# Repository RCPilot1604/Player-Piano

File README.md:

**Work in progress**
Detailed writeup here: https://urbanmakerkraft.com/2024/08/10/player-piano-project-v1/

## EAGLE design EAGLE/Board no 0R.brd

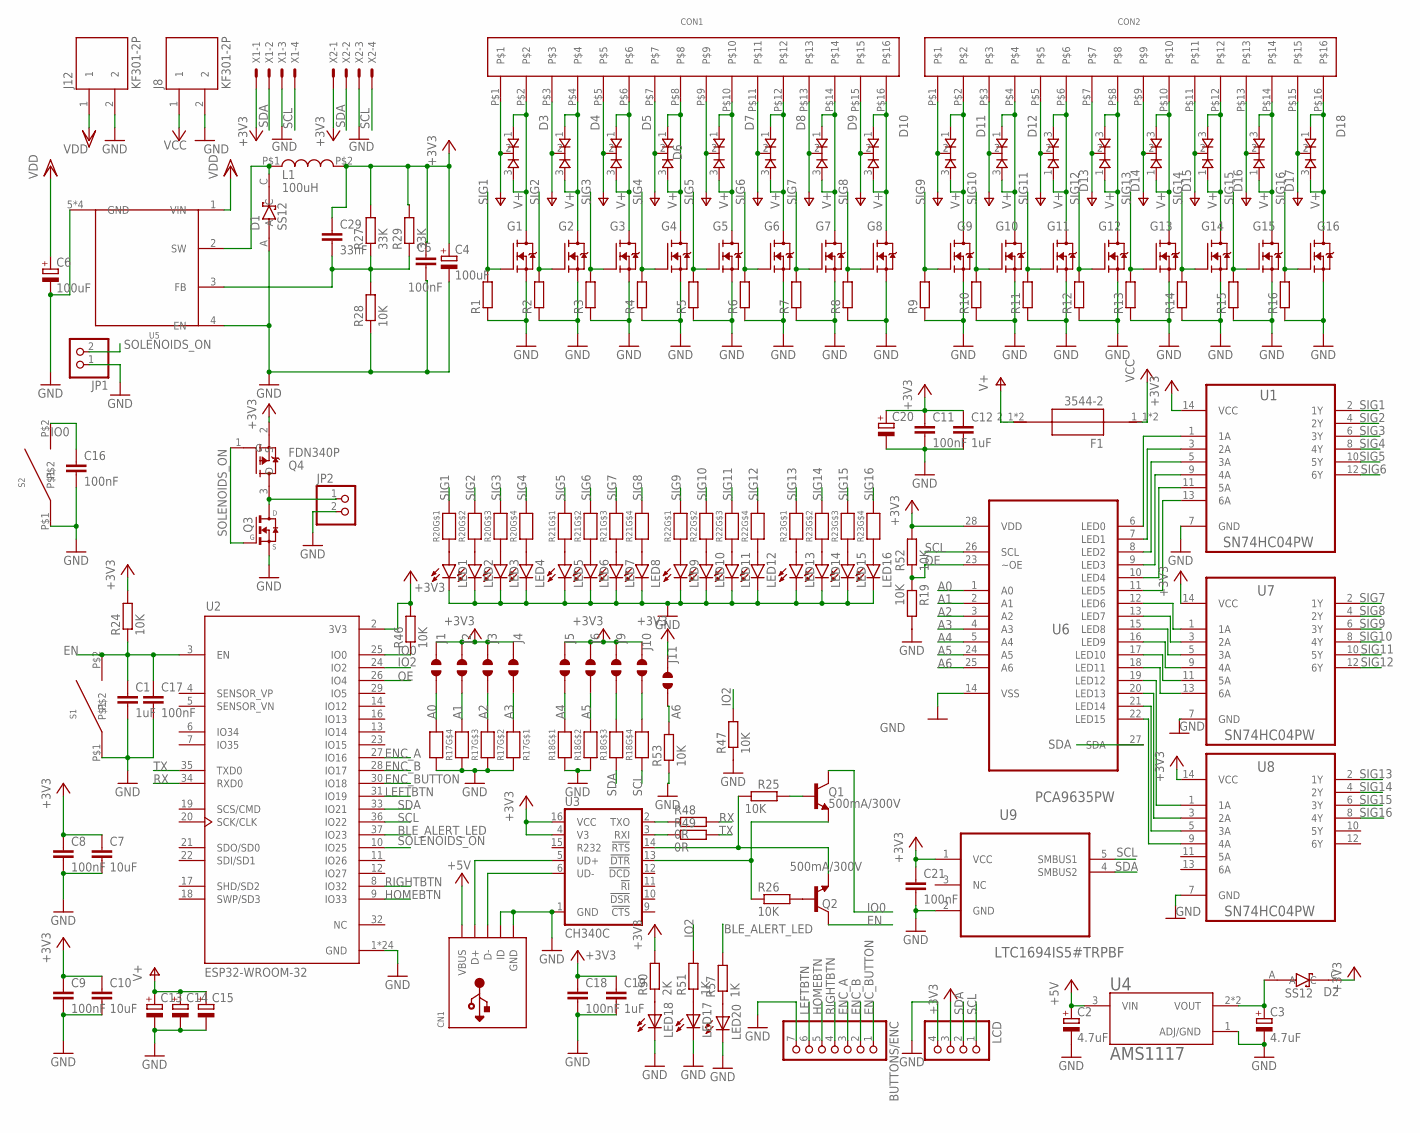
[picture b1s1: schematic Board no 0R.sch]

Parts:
BUTTONS/ENC: PINHD-1X7; 1X07
C1, C12, C19: 1uF; C0603
C2, C3: 4.7uF; C/6032-28R
C4, C6: 100uF; C/6032-28R
C5, C8, C9, C11, C16, C17, C18, C21: 100nF; C0603
C7, C10: 10uF; C0603
C13, C14, C15: CPOL-EUE5-10.5; E5-10,5
C20: CPOL-EUB; PANASONIC_B
C29: 33nF; C0603
CN1: USBMINIB; USB-MINIB
CON1, CON2: 2.54-16P
D1, D2: SS12; DIOM4427X270N
D3, D4, D5, D6, D7, D8, D9, D10, D11, D12, D13, D14, D15, D16, D17, D18: BYQ28E; TO220V
F1: 3544-2; FUSE_3544-2
G1, G2, G3, G4, G5, G6, G7, G8, G9, G10, G11, G12, G13, G14, G15, G16: IRL540N; TO220V
J1, J2, J3, J4, J5, J6, J9, J10, J11: JUMPER_SOLDER_1X2
J8, J12: KF301-2P
JP1, JP2: PINHD-1X2; 1X02
L1: 100uH; CD43
LCD: PINHD-1X4; 1X04
LED1, LED2, LED3, LED4, LED5, LED6, LED7, LED8, LED9, LED10, LED11, LED12, LED13, LED14, LED15, LED16: LEDSMT1206; 1206
LED17, LED18, LED20: LED-0603; LED-603
Q1, Q2: 500mA/300V; SOT23-3
Q3: FDN337N; SSOT-3
Q4: FDN340P; SOT95P240X120-3N
R1, R2, R3, R4, R5, R6, R7, R8, R9, R10, R11, R12, R13, R14, R15, R16: R-EU_R0603; R0603
R17, R18, R20, R21, R22, R23: MICROBUILDER_RESISTOR_4PACK; MICROBUILDER_RESPACK_4X0603
R19: 10K; R1206
R24, R25, R26, R28, R46, R47, R52, R53: 10K; R0603
R27, R29: 33K; R0603
R48, R49: 0R; R0603
R50: 2K; R0603
R51, R57: 1K; R0603
S1, S2: 3X6X2.5
U1, U7, U8: SN74HC04PW; SOP65P640X120-14N
U2: ESP32-WROOM-32; MODULE_ESP32-WROOM-32
U3: CH340C; SO016
U4: AMS1117; SOT229P700X180-4N
U5: XL7005A; SO8
U6: PCA9635PW; SOP65P640X110-28N
U9: LTC1694IS5#TRPBF; SOT95P280X100-5N
X1, X2: JST-XH-04-PIN-LONG-PAD; JST-XH-04-PACKAGE-LONG-PAD

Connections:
+3V3: C4.+, C5.1, C7.1, C8.1, C9.1, C10.1, C11.1, C12.1, C18.1, C19.1, C20.+, C21.1, C29.1, D2.C, J1.1, J2.1, J3.1, J4.1, J5.1, J6.1, J9.1, J10.1, J11.1, L1.P$2, LCD.3, Q4.2 (S), R24.2, R27.2, R29.2, R46.2, R50.2, R52.2, U1.14 (VCC), U2.2 (3V3), U3.4 (V3), U3.16 (VCC), U6.28 (VDD), U7.14 (VCC), U8.14 (VCC), U9.1 (VCC), X1.1, X2.1
+5V: C2.+, CN1.VBUS, U4.3 (VIN)
A0: J1.2, R17.4 (1), U6.1 (A0)
A1: J2.2, R17.3 (1), U6.2 (A1)
A2: J3.2, R17.2 (1), U6.3 (A2)
A3: J4.2, R17.1, U6.4 (A3)
A4: J5.2, R18.8 (2), U6.5 (A4)
A5: J6.2, R18.7 (2), U6.24 (A5)
A6: J11.2, R53.2, U6.25 (A6)
BLE_ALERT_LED: R57.2, U2.37 (IO23)
EN: C1.1, C17.1, Q2.3 (C), R24.1, S1.P$2, U2.3 (EN)
ENC_A: BUTTONS/ENC.3, U2.27 (IO16)
ENC_B: BUTTONS/ENC.2, U2.28 (IO17)
ENC_BUTTON: BUTTONS/ENC.1, U2.30 (IO18)
GND: BUTTONS/ENC.7, C1.2, C2.-, C3.-, C4.-, C5.2, C6.-, C7.2, C8.2, C9.2, C10.2, C11.2, C12.2, C13.-, C14.-, C15.-, C16.2, C17.2, C18.2, C19.2, C20.-, C21.2, CN1.GND, CN1.ID, D1.A, G1.3 (S), G2.3 (S), G3.3 (S), G4.3 (S), G5.3 (S), G6.3 (S), G7.3 (S), G8.3 (S), G9.3 (S), G10.3 (S), G11.3 (S), G12.3 (S), G13.3 (S), G14.3 (S), G15.3 (S), G16.3 (S), J8.2, J12.2, JP1.1, JP2.2, LCD.4, LED1.C, LED2.C, LED3.C, LED4.C, LED5.C, LED6.C, LED7.C, LED8.C, LED9.C, LED10.C, LED11.C, LED12.C, LED13.C, LED14.C, LED15.C, LED16.C, LED17.C, LED18.C, LED20.C, Q3.2 (S), R1.1, R2.1, R3.1, R4.1, R5.1, R6.1, R7.1, R8.1, R9.1, R10.1, R11.1, R12.1, R13.1, R14.1, R15.1, R16.1, R17.5 (2), R17.6 (2), R17.7 (2), R17.8 (2), R18.1, R18.2 (1), R19.2, R28.1, R47.1, R53.1, S1.P$1, S2.P$1, U1.7 (GND), U2.1 (GND), U2.15 (GND), U2.38 (GND), U2.39_1 (GND), U2.39_2 (GND), U2.39_3 (GND), U2.39_4 (GND), U2.39_5 (GND), U2.39_6 (GND), U2.39_7 (GND), U2.39_8 (GND), U2.39_9 (GND), U2.39_10 (GND), U2.39_11 (GND), U2.39_12 (GND), U2.39_13 (GND), U2.39_14 (GND), U2.39_15 (GND), U2.39_16 (GND), U2.39_17 (GND), U2.39_18 (GND), U2.39_19 (GND), U2.39_20 (GND), U2.39_21 (GND), U3.1 (GND), U4.1 (ADJ/GND), U5.4 (EN), U5.5 (GND), U5.6 (GND), U5.7 (GND), U5.8 (GND), U6.14 (VSS), U7.7 (GND), U8.7 (GND), U9.2 (GND), X1.3, X2.3
HOMEBTN: BUTTONS/ENC.5, U2.9 (IO33)
IO0: C16.1, Q1.3 (C), R46.1, S2.P$2, U2.25 (IO0)
IO2: R47.2, R51.2, U2.24 (IO2)
LEFTBTN: BUTTONS/ENC.6, U2.31 (IO19)
unnamed: CON1.P$2, D3.1, D3.3, G1.2 (D)
unnamed: CON1.P$4, D4.1, D4.3, G2.2 (D)
unnamed: CON1.P$6, D5.1, D5.3, G3.2 (D)
unnamed: CON1.P$8, D6.1, D6.3, G4.2 (D)
unnamed: CON1.P$10, D7.1, D7.3, G5.2 (D)
unnamed: CON1.P$12, D8.1, D8.3, G6.2 (D)
unnamed: CON1.P$14, D9.1, D9.3, G7.2 (D)
unnamed: CON1.P$16, D10.1, D10.3, G8.2 (D)
unnamed: CON2.P$2, D11.1, D11.3, G9.2 (D)
unnamed: CON2.P$4, D12.1, D12.3, G10.2 (D)
unnamed: CON2.P$6, D13.1, D13.3, G11.2 (D)
unnamed: CON2.P$8, D14.1, D14.3, G12.2 (D)
unnamed: CON2.P$10, D15.1, D15.3, G13.2 (D)
unnamed: CON2.P$12, D16.1, D16.3, G14.2 (D)
unnamed: CON2.P$14, D17.1, D17.3, G15.2 (D)
unnamed: CON2.P$16, D18.1, D18.3, G16.2 (D)
unnamed: Q1.1 (B), R25.2
unnamed: Q2.1 (B), R26.2
unnamed: LED1.A, R20.1
unnamed: LED2.A, R20.2 (1)
unnamed: LED3.A, R20.3 (1)
unnamed: LED4.A, R20.4 (1)
unnamed: LED5.A, R21.1
unnamed: LED6.A, R21.2 (1)
unnamed: LED7.A, R21.3 (1)
unnamed: LED8.A, R21.4 (1)
unnamed: LED9.A, R22.1
unnamed: LED10.A, R22.2 (1)
unnamed: LED11.A, R22.3 (1)
unnamed: LED12.A, R22.4 (1)
unnamed: LED13.A, R23.1
unnamed: LED14.A, R23.2 (1)
unnamed: LED15.A, R23.3 (1)
unnamed: Q2.2 (E), R25.1, U3.14 (!RTS)
unnamed: Q1.2 (E), R26.1, U3.13 (!DTR)
unnamed: JP2.1, Q3.3 (D), Q4.3 (D)
unnamed: J9.2, R18.6 (2)
unnamed: CN1.D-, U3.6 (UD-)
unnamed: CN1.D+, U3.5 (UD+)
unnamed: J10.2, R18.5 (2)
unnamed: C3.+, D2.A, U4.2 (VOUT), U4.4 (VOUT)
unnamed: LED16.A, R23.4 (1)
unnamed: C29.2, R27.1, R28.2, R29.1, U5.3 (FB)
unnamed: R48.1, U3.2 (TXO)
unnamed: R49.1, U3.3 (RXI)
unnamed: LED20.A, R57.1
unnamed: LED18.A, R50.1
unnamed: LED17.A, R51.1
unnamed: D1.C, L1.P$1, U5.2 (SW)
unnamed: U1.1 (1A), U6.6 (LED0)
unnamed: U1.3 (2A), U6.7 (LED1)
unnamed: U1.5 (3A), U6.8 (LED2)
unnamed: U1.9 (4A), U6.9 (LED3)
unnamed: U1.11 (5A), U6.10 (LED4)
unnamed: U1.13 (6A), U6.11 (LED5)
unnamed: U6.12 (LED6), U7.1 (1A)
unnamed: U6.13 (LED7), U7.3 (2A)
unnamed: U6.15 (LED8), U7.5 (3A)
unnamed: U6.16 (LED9), U7.9 (4A)
unnamed: U6.17 (LED10), U7.11 (5A)
unnamed: U6.18 (LED11), U7.13 (6A)
unnamed: U6.19 (LED12), U8.1 (1A)
unnamed: U6.20 (LED13), U8.3 (2A)
unnamed: U6.21 (LED14), U8.5 (3A)
unnamed: U6.22 (LED15), U8.9 (4A)
OE: R19.1, R52.1, U2.26 (IO4), U6.23 (~OE)
RIGHTBTN: BUTTONS/ENC.4, U2.8 (IO32)
RX: R48.2, U2.34 (RXD0)
SCL: LCD.1, R18.4 (1), U2.36 (IO22), U6.26 (SCL), U9.5 (SMBUS1), X1.4, X2.4
SDA: LCD.2, R18.3 (1), U2.33 (IO21), U6.27 (SDA), U9.4 (SMBUS2), X1.2, X2.2
SIG1: G1.1 (G), R1.2, R20.8 (2), U1.2 (1Y)
SIG2: G2.1 (G), R2.2, R20.7 (2), U1.4 (2Y)
SIG3: G3.1 (G), R3.2, R20.6 (2), U1.6 (3Y)
SIG4: G4.1 (G), R4.2, R20.5 (2), U1.8 (4Y)
SIG5: G5.1 (G), R5.2, R21.8 (2), U1.10 (5Y)
SIG6: G6.1 (G), R6.2, R21.7 (2), U1.12 (6Y)
SIG7: G7.1 (G), R7.2, R21.6 (2), U7.2 (1Y)
SIG8: G8.1 (G), R8.2, R21.5 (2), U7.4 (2Y)
SIG9: G9.1 (G), R9.2, R22.8 (2), U7.6 (3Y)
SIG10: G10.1 (G), R10.2, R22.7 (2), U7.8 (4Y)
SIG11: G11.1 (G), R11.2, R22.6 (2), U7.10 (5Y)
SIG12: G12.1 (G), R12.2, R22.5 (2), U7.12 (6Y)
SIG13: G13.1 (G), R13.2, R23.8 (2), U8.2 (1Y)
SIG14: G14.1 (G), R14.2, R23.7 (2), U8.4 (2Y)
SIG15: G15.1 (G), R15.2, R23.6 (2), U8.6 (3Y)
SIG16: G16.1 (G), R16.2, R23.5 (2), U8.8 (4Y)
SOLENOIDS_ON: JP1.2, Q3.1 (G), Q4.1 (G), U2.10 (IO25)
TX: R49.2, U2.35 (TXD0)
V+: C13.+, C14.+, C15.+, CON1.P$1, CON1.P$3, CON1.P$5, CON1.P$7, CON1.P$9, CON1.P$11, CON1.P$13, CON1.P$15, CON2.P$1, CON2.P$3, CON2.P$5, CON2.P$7, CON2.P$9, CON2.P$11, CON2.P$13, CON2.P$15, D3.2, D4.2, D5.2, D6.2, D7.2, D8.2, D9.2, D10.2, D11.2, D12.2, D13.2, D14.2, D15.2, D16.2, D17.2, D18.2, F1.2_1 (2), F1.2_2 (2)
VCC: F1.1_1 (1), F1.1_2 (1), J8.1
VDD: C6.+, J12.1, U5.1 (VIN)

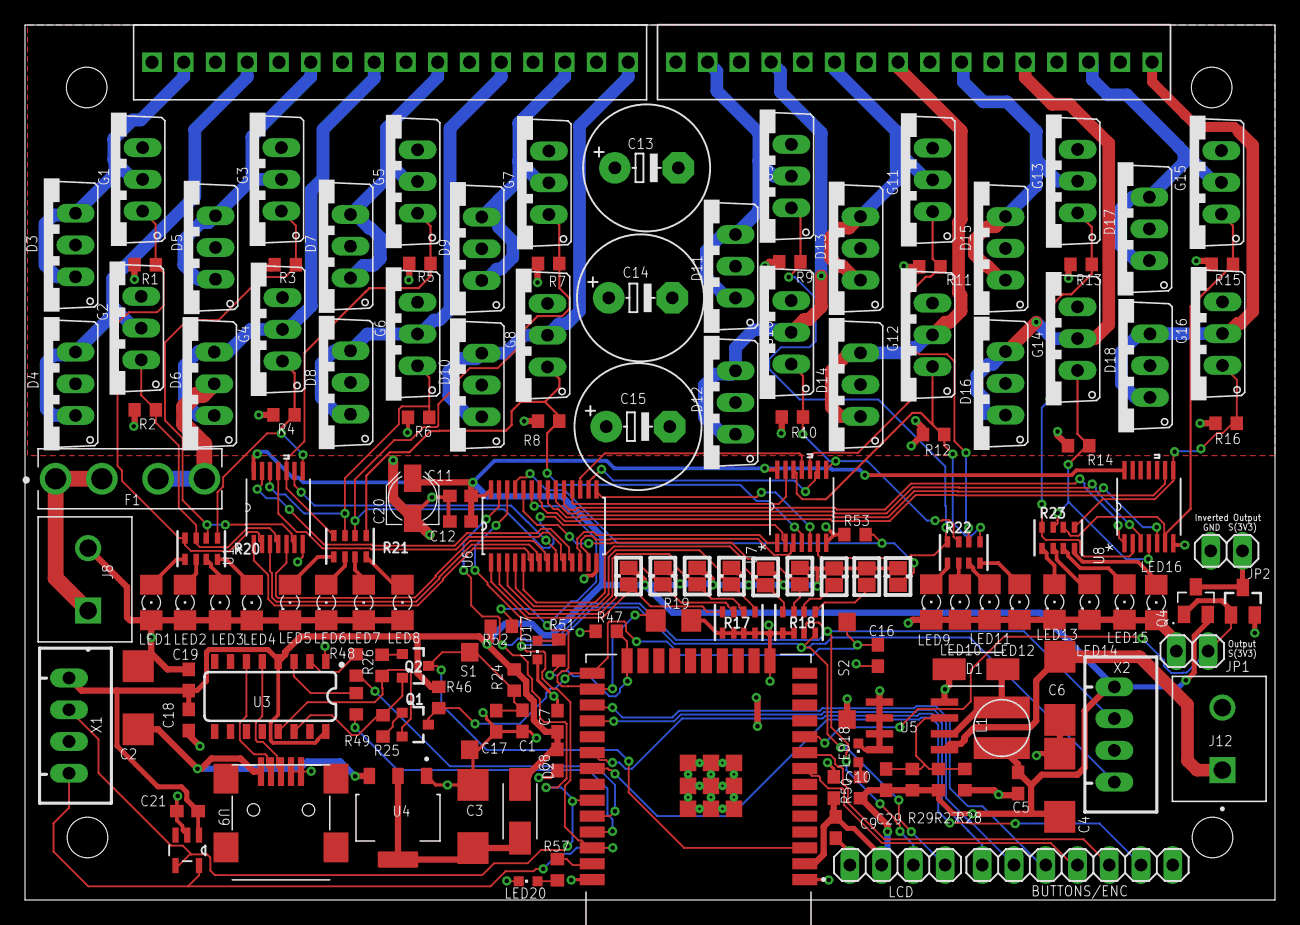
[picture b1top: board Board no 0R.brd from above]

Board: 2 copper layers, 100.0 x 70.0 mm, 150 parts (0 on the bottom side), 110 nets.

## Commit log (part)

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2023-02-26 Uploaded Core Files
2024-07-26 Added EAGLE Schematics and Board
2024-11-28 Move project to PlatformIO
2024-11-28 Add OTA code
2024-11-28 Modify platformio.ini to support OTA
2024-11-28 Revert "Modify platformio.ini to support OTA"
    This reverts commit 33b64bcac83ff1b613ae1a10fc31f8c8ecf34e7c.
2024-11-28 Revert "Modify platformio.ini to support OTA"
    This reverts commit 755e5a1f71e2f7d20dd895e2889f1fe0b89a0f66.
2024-11-28 Revert "Modify platformio.ini to support OTA"
    This reverts commit ddc61f85b01f848f67d19f6b9bc90e0dbcc8eb70.
2024-11-28 Revert "Add OTA code"
    This reverts commit 917316eca735c892ce6f560d217807c2450b0659.
2024-11-28 Revert "Add OTA code"
    This reverts commit bd589469e9066f6d48da46c68686ae0b22e0317d.
2024-11-28 Revert "Add OTA code"
    This reverts commit abb1b36cb25493b9b70972ec5e816aae2f26fecf.
2024-11-28 Change settings for test
2024-11-28 Add bool to track if the previous note is a bounceback
    This is so we can check if the previous note will be able to finish
    since bounceback notes have a different duration as compared to
    normal notes.
2024-11-28 Make cosmetic changes to expression
2024-11-28 Query BB state of previous note
2024-11-28 Add assertions to ensure that previousNoteBB is false
    When lastScheduledState is true, the previous note cannot be BB
    because scheduleBB() sets scheduledState to false.
2024-11-28 Modify main logic to consider case where prev note is BB
    We need to consider a different set of timing requirements
    since BB execution is of a different duration than standard.
    Therefore it could be possible to schedule in another BB if the
    previous note was a BB.
2024-11-28 Modify the current=OFF, previous=OFF condition
    If the current note is OFF and the previous is OFF, we should do
    nothing and just let the OFF carry on.
2024-11-28 Remove extra parameter in Commmand constructor
2024-11-28 Update schedule methods to update lastBounceBackState
2024-11-28 Remove extra printouts
2024-11-28 Remove settings.json from git
2024-11-28 Revert "Modify the current=OFF, previous=OFF condition"
    This reverts commit bfaedefec276a65907df6ce72c604d397b203f72.
2024-11-28 Revert "Modify the current=OFF, previous=OFF condition"
    This reverts commit 196f74e0a20a4b5074b8408f7fad8f2cadd1ec0a.
2024-11-28 Consolidate BOUNCEBACK_DURATION
2024-11-29 Update gitignore
2024-11-29 Make changes
2024-11-29 Modify BB time
2024-11-29 Modify velocity phase voltage
2024-11-29 Remove print for scheduling bounceback
2024-11-29 Modify Note::eraseCommands to return activation time
2024-11-29 Change BB Vel duration from 50 to 10
2024-11-29 Modify BB scheduling to only schedule HOLD when HOLD_DURATION > 0
2024-11-29 Modify scheduling logic
2024-12-24 Add SocketIO Code
2024-12-25 Add logic to handle midi events
2024-12-25 Clean up functions
2024-12-25 Standardize datatypes to avoid redundant casting
2024-12-25 Add logic for handling midi/volume commands
2024-12-25 Modify platformio.ini
2024-12-26 Add cleanup marker
2024-12-26 Add logic for handling noteOn Websocket
2024-12-27 Update logic for handling websocket data
2024-12-27 Remove Display .cpp and .h files
2024-12-27 Remove all references to Display
2024-12-27 Remove LiquidCrystal library
2024-12-27 Fix Display code to remove errors
2024-12-30 Add code to turn off all solenoids after song ends
2024-12-30 Change ip address
2024-12-30 Replace passwords with header file reference
2025-01-03 Modify main.cpp
    Change all BLE-Midi library references
2025-01-03 Remove setMaxDPWM and setMinDPWM
2025-01-03 Add code to initialize vector of notes
2025-01-03 Change byte to uint8_t
2025-01-03 Remove setMaxDPWM and setMinDPWM and directly assign
2025-01-10 Enable debug
2025-01-10 Update EAGLE files to latest version
2025-01-10 Add CAD files
2025-01-24 Make minor edits to platform.ini and settings.json
2026-05-29 Add git-filter-repo.txt to .gitignore

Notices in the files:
parts and their libraries:
SparkFun-DiscreteSemi: Licensing: Creative Commons ShareAlike 4.0 International - https://creativecommons.org/licenses/by-sa/4.0
